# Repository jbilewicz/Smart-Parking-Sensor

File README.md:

#  Smart Parking Sensor

## 📝 Project Overview
This is an advanced parking assistance system designed as a mechatronic project. It combines high-accuracy ultrasonic distance sensing with a smooth graphical interface.

The system features an **Exponential Moving Average (EMA)** filter to eliminate sensor noise and a **Fast Response** algorithm for immediate emergency detection.

##  Tech Stack

---

##  Components Used
- **Microcontroller:** ESP32 (DEVKITV1).
- **Distance Sensor:** HC-SR04 Ultrasonic module.
- **Display:** SSD1306 128x64 OLED (I2C) for real-time bar animation.
- **Indicators:**
  - 🟢 **Green LED:** Safe distance (>30cm).
  - 🟡 **Yellow LED:** Caution (20-30cm).
  - 🔴 **Red LED:** Danger (<20cm).
- **Audio:** Active Buzzer (**F/CM12P**) with dynamic frequency.
- **Control:** Hardware **Mute Button** for sound toggling.

---

##  Hardware Design
The PCB was designed in **Autodesk EAGLE** with a focus on durability and clean layout:
- **Board Dimensions:** 180 x 70 mm.
- **Mounting:** 4x 3.2mm symmetric holes for M3 screws.
- **Layout:** Optimized 2.54mm grid for prototyping consistency.

###  Pinout Table
| Component | Pin | Note |
| :--- | :--- | :--- |
| **HC-SR04 Trig** | GPIO 5 | Output Trigger |
| **HC-SR04 Echo** | GPIO 18 | Input Echo |
| **OLED SDA** | GPIO 21 | I2C Data |
| **OLED SCL** | GPIO 22 | I2C Clock |
| **Buzzer (+)** | GPIO 27 | PWM Tone Control |
| **Mute Button** | GPIO 4 | Internal Pull-up |
| **LEDs (G, Y, R)**| 13, 12, 14 | Digital Indicators |

---

##  Software Logic
The firmware includes:
1. **Signal Smoothing:** Prevents the progress bar from flickering using software-based EMA.
2. **Fast Response:** Instantly updates if the distance changes by >15cm to handle rapid movements.
3. **Dynamic Beeping:** The closer the object, the higher the tone and shorter the delay.

---

##  Repository Structure
- `/Firmware` - Arduino source code (.ino).
- `/Hardware` - EAGLE schematic (.sch) and board (.brd) files.
- `/Exports` - Visualizations, PDF schematics, and PCB renders.

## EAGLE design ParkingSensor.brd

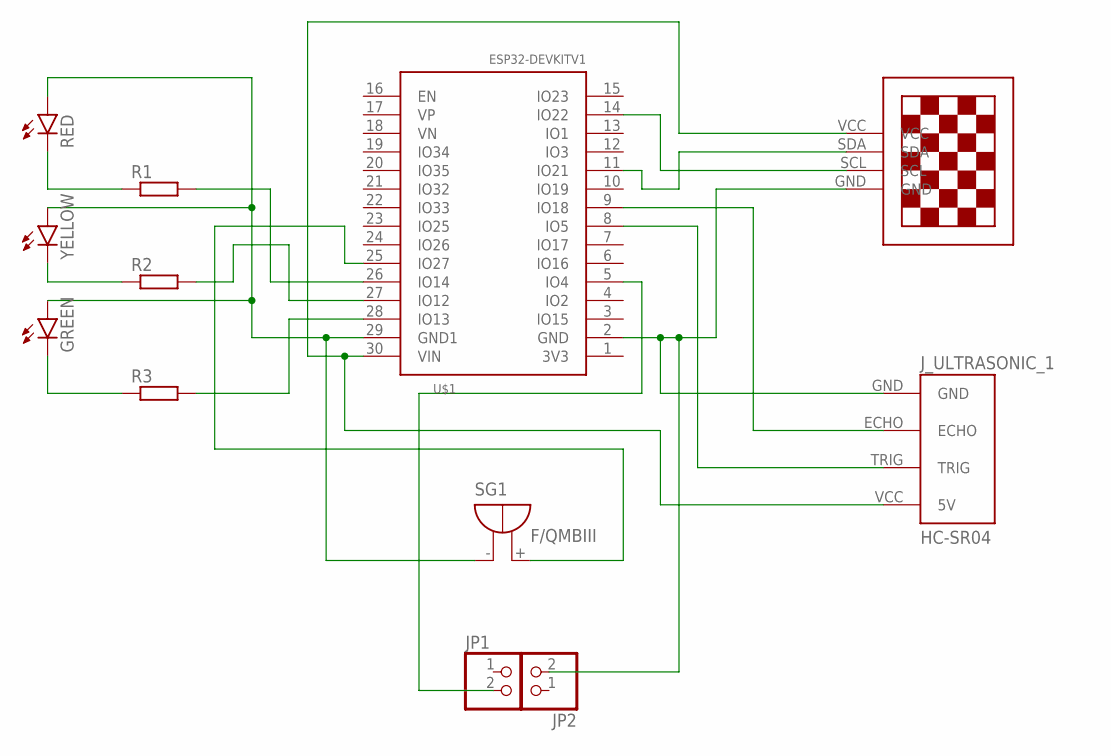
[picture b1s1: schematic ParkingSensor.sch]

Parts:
GREEN: LED5MM
JP1, JP2: PINHD-1X2; 1X02
J_ULTRASONIC_1: HC-SR04; HC-SR04_FOOTPRINT
R1, R2, R3: R-EU_0204/7; 0204/7
RED: LED5MM
SG1: F/QMBIII
U$1: ESP32DEVKITV1; ESP32-DEVKITV1
U$3: 13"OLED13"OLED; 1.3"OLED
YELLOW: LED5MM

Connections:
unnamed: JP2.2, J_ULTRASONIC_1.GND, U$1.2 (GND), U$3.GND
unnamed: J_ULTRASONIC_1.VCC (5V), U$1.30 (VIN), U$3.VCC
unnamed: U$1.14 (IO22), U$3.SCL
unnamed: U$1.11 (IO21), U$3.SDA
unnamed: SG1.+ (-), U$1.25 (IO27)
unnamed: J_ULTRASONIC_1.TRIG, U$1.8 (IO5)
unnamed: J_ULTRASONIC_1.ECHO, U$1.9 (IO18)
unnamed: GREEN.K (C), R3.1
unnamed: R2.1, YELLOW.K (C)
unnamed: R1.1, RED.K (C)
unnamed: R1.2, U$1.26 (IO14)
unnamed: R2.2, U$1.27 (IO12)
unnamed: R3.2, U$1.28 (IO13)
unnamed: GREEN.A, RED.A, SG1.- (+), U$1.29 (GND1), YELLOW.A
unnamed: JP1.2, U$1.5 (IO4)

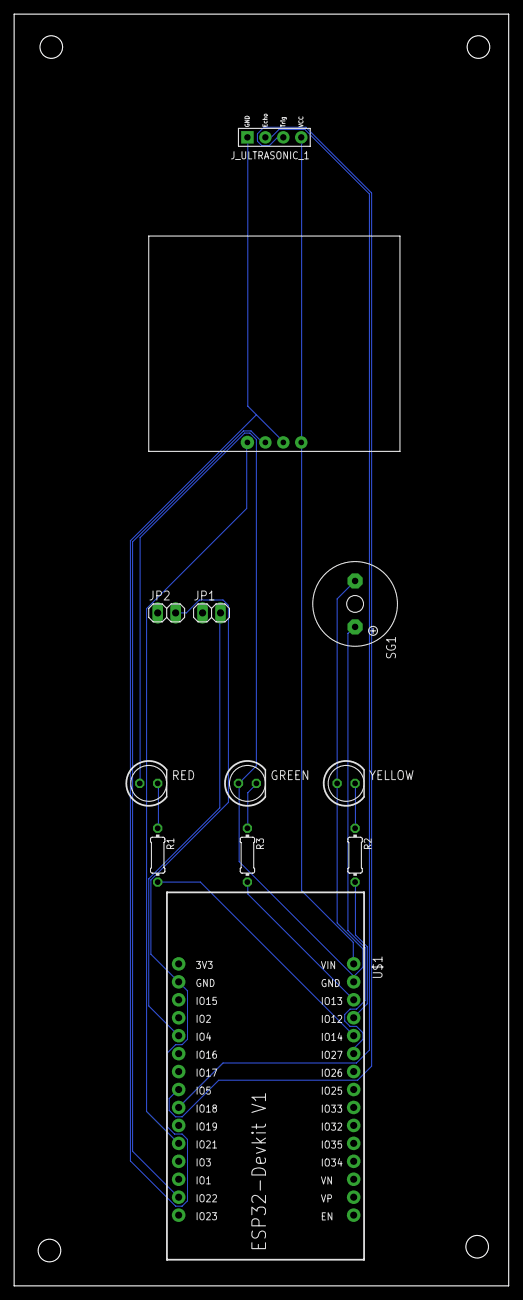
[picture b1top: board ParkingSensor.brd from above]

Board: 2 copper layers, 70.0 x 180.0 mm, 12 parts (0 on the bottom side), 15 nets.

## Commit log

2026-02-15 Simplify project title in README
    Removed unnecessary details from the project title.
